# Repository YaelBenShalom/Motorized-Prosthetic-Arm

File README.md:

# The Design and Control of a Motorized Prosthetic Arm

Author: Yael Ben Shalom<br>
Final project, MS in Robotics at Northwestern, 2021.

## Table of Contents

- [Project Description](#project-description)
- [Project Overview](#project-overview)
- [Getting Started](#getting-started)

## Project Description

In this project, I designed, built, and controlled a motorized prosthetic elbow that imitates healthy arm motion to help amputees prevent falling, avoid injuries, and maintain balance while walking. According to [Kent and Major's research](https://www.sciencedirect.com/science/article/abs/pii/S0268003320301248?casa_token=pASJip1O0HgAAAAA:ckojZ8F55NSTF2rAq7aVUub568BDZgnYYnto9notnVSgfjbTsNp5ktE2Q-ZMWgL62Lgc80yd), asymmetries in body mass and motion affect the regulation of whole-body angular momentum in individuals with upper limb absence and may increase fall risk.

To better predict the arm-body motion, I analyzed arm movement data patterns, simulated full arm dynamics, and found the relation between walking speed to the angular velocity of the arm.

Please visit [my website](https://yaelbenshalom.github.io/motorized_prosthetic_arm/index.html) for more information about this project.

## Project Overview

This project contains 4 parts:

1. [Data collection](https://github.com/YaelBenShalom/Motorized-Prosthetic-Arm/tree/master/data)
2. [Arm motion analysis and modeling](https://github.com/YaelBenShalom/Motorized-Prosthetic-Arm/tree/master/motor_control/arm_pendulum_modeling)
3. [Motor control to achieve the desired arm motion](https://github.com/YaelBenShalom/Motorized-Prosthetic-Arm/tree/master/motor_control)
4. [Mechanical design of the prosthetic elbow](https://github.com/YaelBenShalom/Motorized-Prosthetic-Arm/tree/master/mech_design)

## Getting Started

1. Clone the repository:
    ```
    git clone https://github.com/YaelBenShalom/Motorized-Prosthetic-Arm.git
    ```

2. Install the `odrive-tool` package. For installation instructions, visit the [ODrive getting-started page](https://docs.odriverobotics.com/).

3. Assemble the system according to the system sketch.

4. Connect the module to the computer's USB port and upload the desired ODrive configuration by running:
    ```
    python3 setup.py
    ```

    The controller might need an additional tunning. Follow the tunning instructions on the [ODrive control page](https://docs.odriverobotics.com/control).

5. Activate the system by running:
    ```
    python3 motor_control/odrive_control.py --velocity=<walking velocity>
    ```

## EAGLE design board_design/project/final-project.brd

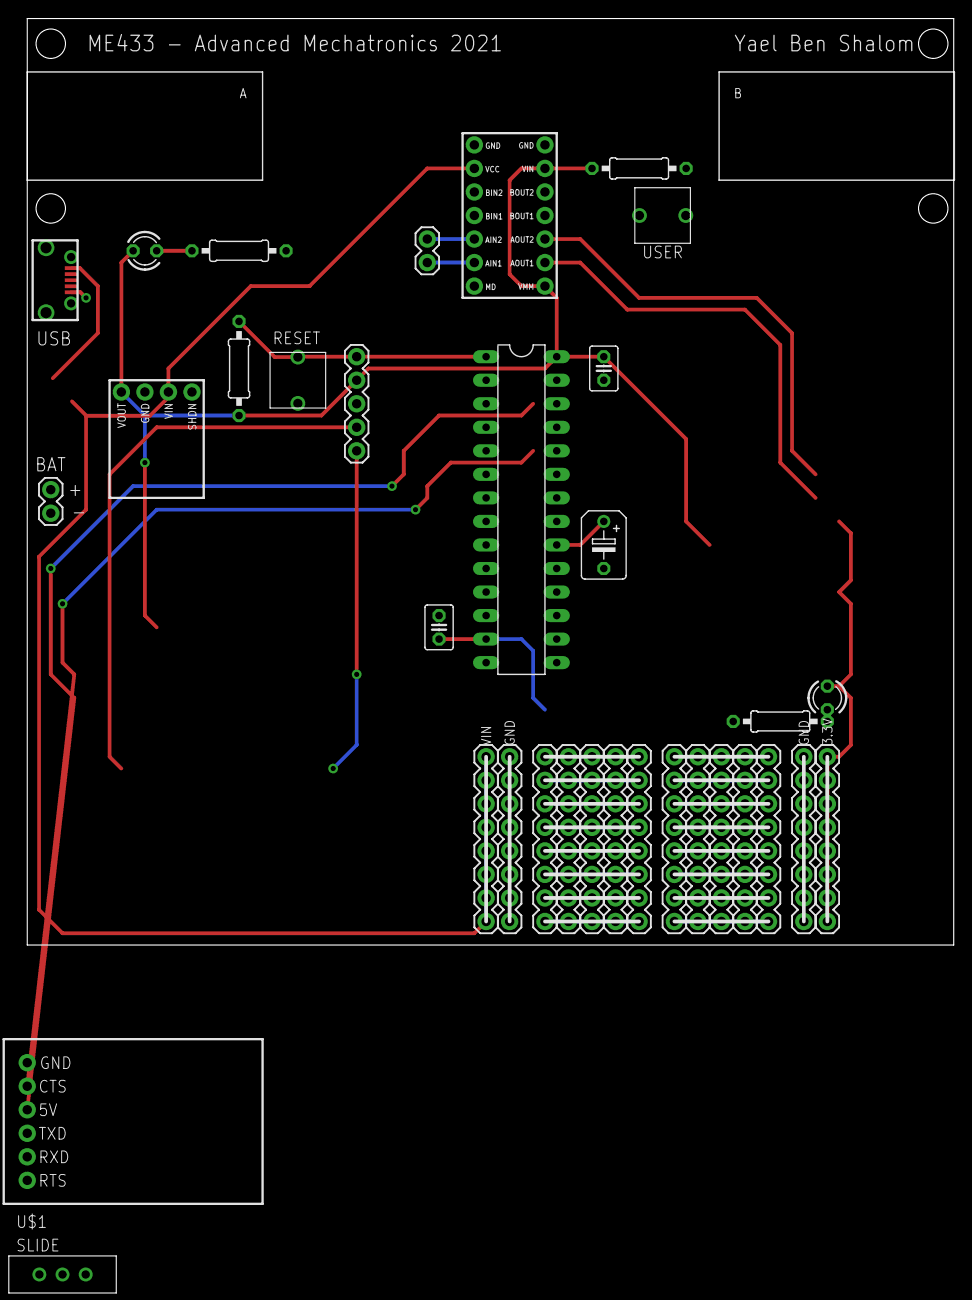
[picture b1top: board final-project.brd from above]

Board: 2 copper layers, 100.0 x 100.0 mm, 34 parts (0 on the bottom side), 34 nets.

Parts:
BAT: 1X02
C1, C2: 0.1uF; C025-030X050
C3: 10uF; B45181B
J2: A; 1X02
J16, J17, J18, J19, J20, J21, J22, J23, J24, J25, J26, J27, J28, J29: 1X08
LED1: RED; LED3MM
LED2: GREEN; LED3MM
R1, R5: 330; 0207/10
R2, R6: 10k; 0207/10
U1: PIC32MX170F256B; DIL28-3
U$1: SLIDE
U$2: POLOLU3V3
U$4: SNAP
U$5: RESET; PUSH
U$6: FRIEND
U$9: USER; PUSH
U$10: POLOLU
U$12: MICROUSB

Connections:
+3V3: C1.1, C2.1, J26.1, J26.2, J26.3, J26.4, J26.5, J26.6, J26.7, J26.8, LED1.A, LED2.A, R2.2, R6.2, U1.3, U1.13, U1.28, U$2.1, U$4.2, U$10.8, U$10.13
+5V: U$1.1, U$12.1.VBUS
A2-ADIR: U1.9, U$10.9
A3-APWM: U1.10, U$10.10
B0-PGD: U1.4, U$4.4
B1-PGC: U1.5, U$4.5
B13-RXD: U1.24, U$6.2
B15-TXD: U1.26, U$6.3
GND: BAT.1, C1.2, C2.2, C3.-, J27.1, J27.2, J27.3, J27.4, J27.5, J27.6, J27.7, J27.8, J28.1, J28.2, J28.3, J28.4, J28.5, J28.6, J28.7, J28.8, R1.1, R5.1, U1.8, U1.19, U1.27, U$2.2, U$4.3, U$5.P$1, U$6.6, U$9.P$1, U$10.1, U$10.14, U$12.5.GND
MCLR: R2.1, U1.1, U$4.1, U$5.P$2
MCLR1: R6.1, U1.2, U$9.P$2
unnamed: LED1.K, R1.2
unnamed: C3.+, U1.20
unnamed: LED2.K, R5.2
unnamed: J2.1, U$10.6
unnamed: J2.2, U$10.5
unnamed: J16.8, J17.8, J18.8, J19.8, J20.8
unnamed: J16.7, J17.7, J18.7, J19.7, J20.7
unnamed: J16.6, J17.6, J18.6, J19.6, J20.6
unnamed: J16.5, J17.5, J18.5, J19.5, J20.5
unnamed: J16.4, J17.4, J18.4, J19.4, J20.4
unnamed: J16.3, J17.3, J18.3, J19.3, J20.3
unnamed: J16.2, J17.2, J18.2, J19.2, J20.2
unnamed: J16.1, J17.1, J18.1, J19.1, J20.1
unnamed: J21.8, J22.8, J23.8, J24.8, J25.8
unnamed: J21.7, J22.7, J23.7, J24.7, J25.7
unnamed: J21.6, J22.6, J23.6, J24.6, J25.6
unnamed: J21.5, J22.5, J23.5, J24.5, J25.5
unnamed: J21.4, J22.4, J23.4, J24.4, J25.4
unnamed: J21.3, J22.3, J23.3, J24.3, J25.3
unnamed: J21.2, J22.2, J23.2, J24.2, J25.2
unnamed: J21.1, J22.1, J23.1, J24.1, J25.1
V+: BAT.2, U$1.3
VIN: J29.1, J29.2, J29.3, J29.4, J29.5, J29.6, J29.7, J29.8, U$1.2, U$2.3, U$10.2

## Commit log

2021-05-17 add the data and jupyter notebook
2021-05-17 update jupyter notebook
2021-05-24 add data-reading script and update jupyter notebook
2021-05-27 update notebook
2021-06-03 add mech design repo
2021-06-09 add board design files
2021-06-10 add mech design
2021-06-10 add board lobraries
2021-09-20 update calculations
2021-09-20 organize repo
2021-09-24 update mech design
2021-09-29 add ODrive submodule
2021-09-29 add diagrams
2021-09-30 add calculations
2021-09-30 remove submodule
2021-09-30 add backup-config
2021-10-01 add odrive_control script
2021-10-04 update motor_control script
2021-10-04 add ODrive
2021-10-04 update submodule
2021-10-04 add submodule ODrive
2021-10-04 update file names
2021-10-04 add mechatronics board
2021-10-04 update data scripts
2021-10-04 remove jupyter notebook
2021-10-04 add install file
2021-10-06 update model & control
2021-10-06 update pendulum script
2021-10-06 add a test bracket dxf
2021-10-07 update control script
2021-10-07 add ul-amp-walk-assist submodule
2021-10-11 add motor_control branch
2021-10-12 update test files
2021-10-12 add requirements
2021-10-12 add calibration
2021-10-12 add walking data
2021-10-14 add velocity + torque control videos
2021-10-15 add hand-back motion data
2021-10-15 add txt to csv converter
2021-10-15 add new data
2021-10-19 update arm-modeling calculation
2021-10-19 update data
2021-10-19 update arm modeling
2021-10-20 update data processing
2021-10-21 update odrive control
2021-10-21 add videos
2021-10-22 update arm model
2021-10-22 add single pendulum arm modeling
2021-10-22 update single pendulum arm modeling
2021-10-22 update CAD model
2021-10-23 remove .ipynb from history
2021-10-25 update c scripts
2021-10-25 update python aem modeling scripts
2021-10-25 update jupyter script
2021-10-26 add setup file
2021-10-26 reformat files
2021-10-27 add pid controller
2021-10-27 update pid controller
2021-10-27 remove .vscode
2021-10-28 update odrive config
2021-10-28 remove image
2021-11-01 update formatting
2021-11-01 add motor selection to jupyter notebook
2021-11-01 update system block diagram
2021-11-02 update control loop
2021-11-02 tune motor
2021-11-04 tune controller
2021-11-09 tune pid controller
2021-11-22 add treadmill testing
2021-11-22 fix angle error in input_pos_plot
2021-11-23 add data script
2021-11-23 add fix frequency
2021-11-29 add treadmill graphs
2021-11-30 update motorized prosthetic project
2021-12-02 update position control
2021-12-02 remove data script
2021-12-02 update video folder
2021-12-04 remove unused videos
2021-12-09 remove unused data
2022-03-06 update media
2022-03-13 fix typos
